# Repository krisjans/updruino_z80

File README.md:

# updruino_z80
Use Updruino FPGA boarad (iCE40-UP5K-SG48) as bridge between ZX Spectrum and Raspberry Pi

# warning!
This project uses iCE40-UP5K-SG48 in "CRAM" mode.

By default Updruino ships in "flash mode".

You must re-solder two 0Ohm resistors from Horizontal "Flash" positions to vertical "CRAM" positions.

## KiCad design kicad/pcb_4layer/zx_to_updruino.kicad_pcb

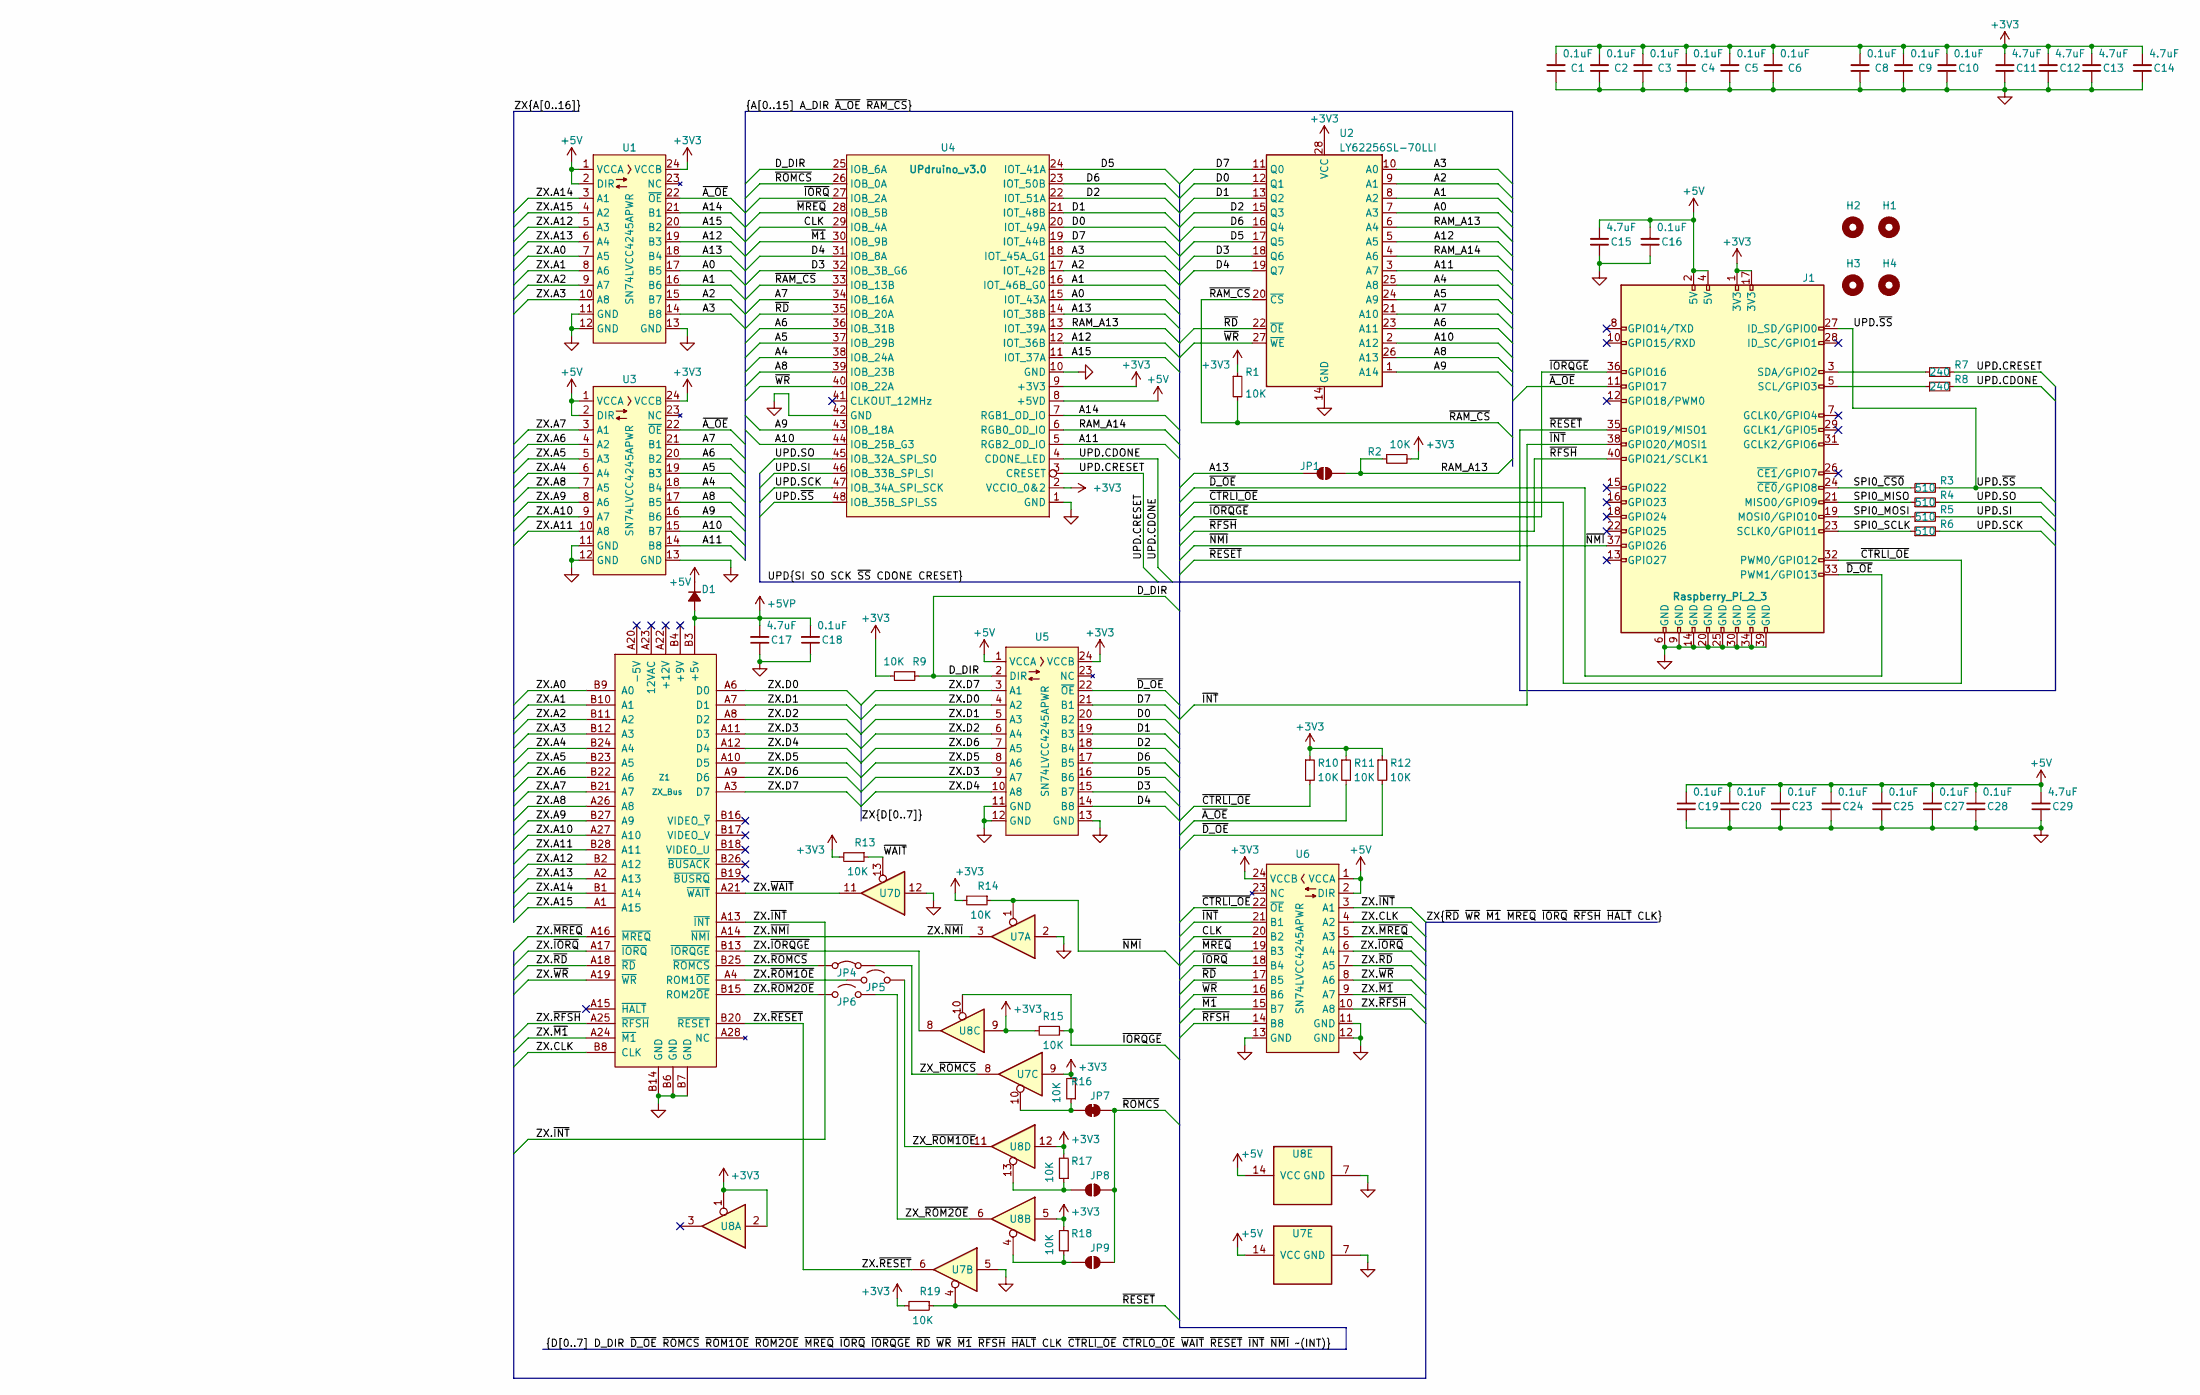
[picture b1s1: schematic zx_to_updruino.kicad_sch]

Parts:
C1, C2, C3, C4, C5, C6, C8, C9, C10, C16, C18, C19, C20, C23, C24, C25, C27, C28: 0.1uF; C_0805_2012Metric
C11, C12, C13, C14, C15, C17, C29: 4.7uF; C_0805_2012Metric
D1: B5819W SL; D_SOD-123; LCSC C8598
H1, H2, H3, H4: MountingHole
J1: Raspberry_Pi_2_3; PinSocket_2x20_P2.54mm_Vertical
JP1, JP8, JP9: SolderJumper_2_Bridged; SolderJumper-2_P1.3mm_Open_RoundedPad1.0x1.5mm
JP4, JP5, JP6: Jumper_2_Bridged; PinSocket_1x02_P2.54mm_Vertical
JP7: SolderJumper_2_Bridged; SolderJumper-2_P1.3mm_Bridged_RoundedPad1.0x1.5mm
R1, R2, R9, R10, R11, R12, R13, R14, R15, R16, R17, R18, R19: 10K; R_1206_3216Metric
R3, R4, R5, R6: 510; R_0805_2012Metric
R7, R8: 240; R_0805_2012Metric
U1, U3, U5, U6: SN74LVCC4245APWR; TSSOP-24_L7.8-W4.4-P0.65-LS6.4-BL; LCSC C7035
U2: LY62256SL-70LLI; SOP-28_L18.2-W8.5-P1.27-LS12.1-BL; LCSC C261868
U4: UPdruino_v3.0
U7, U8: 74HC125D; SOIC-14_L8.7-W3.9-P1.27-LS6.0-BL; LCSC C5598
Z1: ZX_Bus; ZX_Bus_Edge_Connector

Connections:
+3V3: C1.2, C2.2, C3.2, C4.2, C5.2, C6.2, C8.2, C9.2, C10.2, C11.2, C12.2, C13.2, C14.2, J1.1 (3V3), J1.17 (3V3), R1.1, R2.2, R9.2, R10.1, R11.1, R12.1, R13.2, R14.2, R15.2, R16.2, R17.2, R18.2, R19.2, U1.24 (VCCB), U2.28 (VCC), U3.24 (VCCB), U4.2 (VCCIO_0&2), U4.9 (+3V3), U5.24 (VCCB), U6.24 (VCCB), U7.9, U8.1, U8.2, U8.5, U8.9, U8.12
+5V: C15.2, C16.2, C19.2, C20.2, C23.2, C24.2, C25.2, C27.2, C28.2, C29.2, D1.1 (K), J1.2 (5V), J1.4 (5V), U1.1 (VCCA), U1.2 (DIR), U3.1 (VCCA), U3.2 (DIR), U4.8 (+5VD), U5.1 (VCCA), U6.1 (VCCA), U6.2 (DIR), U7.14 (VCC), U8.14 (VCC)
+5VP: C17.2, C18.2, D1.2 (A), Z1.B3 (+5v)
/A0: U1.17 (B5), U2.7 (A3), U4.15 (IOT_43A)
/A1: U1.16 (B6), U2.8 (A2), U4.16 (IOT_46B_G0)
/A2: U1.15 (B7), U2.9 (A1), U4.17 (IOT_42B)
/A3: U1.14 (B8), U2.10 (A0), U4.18 (IOT_45A_G1)
/A4: U2.25 (A8), U3.18 (B4), U4.38 (IOB_24A)
/A5: U2.24 (A9), U3.19 (B3), U4.37 (IOB_29B)
/A6: U2.23 (A11), U3.20 (B2), U4.36 (IOB_31B)
/A7: U2.21 (A10), U3.21 (B1), U4.34 (IOB_16A)
/A8: U2.26 (A13), U3.17 (B5), U4.39 (IOB_23B)
/A9: U2.1 (A14), U3.16 (B6), U4.43 (IOB_18A)
/A10: U2.2 (A12), U3.15 (B7), U4.44 (IOB_25B_G3)
/A11: U2.3 (A7), U3.14 (B8), U4.5 (RGB2_OD_IO)
/A12: U1.19 (B3), U2.5 (A5), U4.12 (IOT_36B)
/A13: JP1.1 (A), U1.18 (B4), U4.14 (IOT_38B)
/A14: U1.21 (B1), U4.7 (RGB1_OD_IO)
/A15: U1.20 (B2), U4.11 (IOT_37A)
/CLK: U4.29 (IOB_4A), U6.20 (B2)
/D0: U2.12 (Q1), U4.20 (IOT_49A), U5.20 (B2)
/D1: U2.13 (Q2), U4.21 (IOT_48B), U5.19 (B3)
/D2: U2.15 (Q3), U4.22 (IOT_51A), U5.18 (B4)
/D3: U2.18 (Q6), U4.32 (IOB_3B_G6), U5.15 (B7)
/D4: U2.19 (Q7), U4.31 (IOB_8A), U5.14 (B8)
/D5: U2.17 (Q5), U4.24 (IOT_41A), U5.16 (B6)
/D6: U2.16 (Q4), U4.23 (IOT_50B), U5.17 (B5)
/D7: U2.11 (Q0), U4.19 (IOT_44B), U5.21 (B1)
/D_DIR: R9.1, U4.25 (IOB_6A), U5.2 (DIR)
/RAM_A13: JP1.2 (B), R2.1, U2.6 (A4), U4.13 (IOT_39A)
/RAM_A14: U2.4 (A6), U4.6 (RGB0_OD_IO)
/SPI0_MISO: J1.21 (MISO0/GPIO9), R4.1
/SPI0_MOSI: J1.19 (MOSI0/GPIO10), R5.1
/SPI0_SCLK: J1.23 (SCLK0/GPIO11), R6.1
/SPI0_~CS0: J1.24 (~CE0/GPIO8), R3.1
/UPD.CDONE: R8.2, U4.4 (CDONE_LED)
/UPD.CRESET: R7.2, U4.3 (CRESET)
/UPD.SCK: R6.2, U4.47 (IOB_34A_SPI_SCK)
/UPD.SI: R5.2, U4.46 (IOB_33B_SPI_SI)
/UPD.SO: R4.2, U4.45 (IOB_32A_SPI_SO)
/UPD.~SS: J1.27 (ID_SD/GPIO0), R3.2, U4.48 (IOB_35B_SPI_SS)
/ZX.A0: U1.7 (A5), Z1.B9 (A0)
/ZX.A1: U1.8 (A6), Z1.B10 (A1)
/ZX.A2: U1.9 (A7), Z1.B11 (A2)
/ZX.A3: U1.10 (A8), Z1.B12 (A3)
/ZX.A4: U3.6 (A4), Z1.B24 (A4)
/ZX.A5: U3.5 (A3), Z1.B23 (A5)
/ZX.A6: U3.4 (A2), Z1.B22 (A6)
/ZX.A7: U3.3 (A1), Z1.B21 (A7)
/ZX.A8: U3.7 (A5), Z1.A26 (A8)
/ZX.A9: U3.8 (A6), Z1.B27 (A9)
/ZX.A10: U3.9 (A7), Z1.A27 (A10)
/ZX.A11: U3.10 (A8), Z1.B28 (A11)
/ZX.A12: U1.5 (A3), Z1.B2 (A12)
/ZX.A13: U1.6 (A4), Z1.A2 (A13)
/ZX.A14: U1.3 (A1), Z1.B1 (A14)
/ZX.A15: U1.4 (A2), Z1.A1 (A15)
/ZX.CLK: U6.4 (A2), Z1.B8 (CLK)
/ZX.D0: U5.4 (A2), Z1.A6 (D0)
/ZX.D1: U5.5 (A3), Z1.A7 (D1)
/ZX.D2: U5.6 (A4), Z1.A8 (D2)
/ZX.D3: U5.9 (A7), Z1.A11 (D3)
/ZX.D4: U5.10 (A8), Z1.A12 (D4)
/ZX.D5: U5.8 (A6), Z1.A10 (D5)
/ZX.D6: U5.7 (A5), Z1.A9 (D6)
/ZX.D7: U5.3 (A1), Z1.A3 (D7)
/ZX.~INT: U6.3 (A1), Z1.A13 (~INT)
/ZX.~IORQGE: U8.8, Z1.B13 (~IORQGE)
/ZX.~IORQ: U6.6 (A4), Z1.A17 (~IORQ)
/ZX.~M1: U6.9 (A7), Z1.A24 (~M1)
/ZX.~MREQ: U6.5 (A3), Z1.A16 (~MREQ)
/ZX.~NMI: U7.3, Z1.A14 (~NMI)
/ZX.~RD: U6.7 (A5), Z1.A18 (~RD)
/ZX.~RESET: U7.6, Z1.B20 (~RESET)
/ZX.~RFSH: U6.10 (A8), Z1.A25 (~RFSH)
/ZX.~ROM1OE: JP5.1 (A), Z1.A4 (ROM1~OE)
/ZX.~ROM2OE: JP6.1 (A), Z1.B15 (ROM2~OE)
/ZX.~ROMCS: JP4.1 (A), Z1.B25 (~ROMCS)
/ZX.~WAIT: U7.11, Z1.A21 (~WAIT)
/ZX.~WR: U6.8 (A6), Z1.A19 (~WR)
/ZX_~ROM1OE: JP5.2 (B), U8.11
/ZX_~ROM2OE: JP6.2 (B), U8.6
/ZX_~ROMCS: JP4.2 (B), U7.8
/~A_OE: J1.11 (GPIO17), R11.2, U1.22 (~OE), U3.22 (~OE)
/~CTRLI_OE: J1.32 (PWM0/GPIO12), R10.2, U6.22 (~OE)
/~INT: J1.38 (GPIO20/MOSI1), U6.21 (B1)
/~IORQGE: J1.36 (GPIO16), R15.1, U8.10
/~IORQ: U4.27 (IOB_2A), U6.18 (B4)
/~M1: U4.30 (IOB_9B), U6.15 (B7)
/~MREQ: U4.28 (IOB_5B), U6.19 (B3)
/~RAM_CS: R1.2, U2.20 (~CS), U4.33 (IOB_13B)
/~RD: U2.22 (~OE), U4.35 (IOB_20A), U6.17 (B5)
/~RESET: J1.35 (GPIO19/MISO1), R19.1, U7.4
/~RFSH: J1.40 (GPIO21/SCLK1), U6.14 (B8)
/~ROMCS: JP7.1 (A), JP8.2 (B), JP9.2 (B), U4.26 (IOB_0A)
/~WAIT: R13.1, U7.13
/~WR: U2.27 (~WE), U4.40 (IOB_22A), U6.16 (B6)
GND: C1.1, C2.1, C3.1, C4.1, C5.1, C6.1, C8.1, C9.1, C10.1, C11.1, C12.1, C13.1, C14.1, C15.1, C16.1, C17.1, C18.1, C19.1, C20.1, C23.1, C24.1, C25.1, C27.1, C28.1, C29.1, J1.6 (GND), J1.9 (GND), J1.14 (GND), J1.20 (GND), J1.25 (GND), J1.30 (GND), J1.34 (GND), J1.39 (GND), U1.11 (GND), U1.12 (GND), U1.13 (GND), U2.14 (GND), U3.11 (GND), U3.12 (GND), U3.13 (GND), U4.1 (GND), U4.10 (GND), U4.42 (GND), U5.11 (GND), U5.12 (GND), U5.13 (GND), U6.11 (GND), U6.12 (GND), U6.13 (GND), U7.2, U7.5, U7.7 (GND), U7.12, U8.7 (GND), Z1.B6 (GND), Z1.B7 (GND), Z1.B14 (GND)
unnamed: J1.3 (SDA/GPIO2), R7.1
unnamed: J1.5 (SCL/GPIO3), R8.1
unnamed: JP7.2 (B), R16.1, U7.10
unnamed: JP8.1 (A), R17.1, U8.13
unnamed: JP9.1 (A), R18.1, U8.4

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
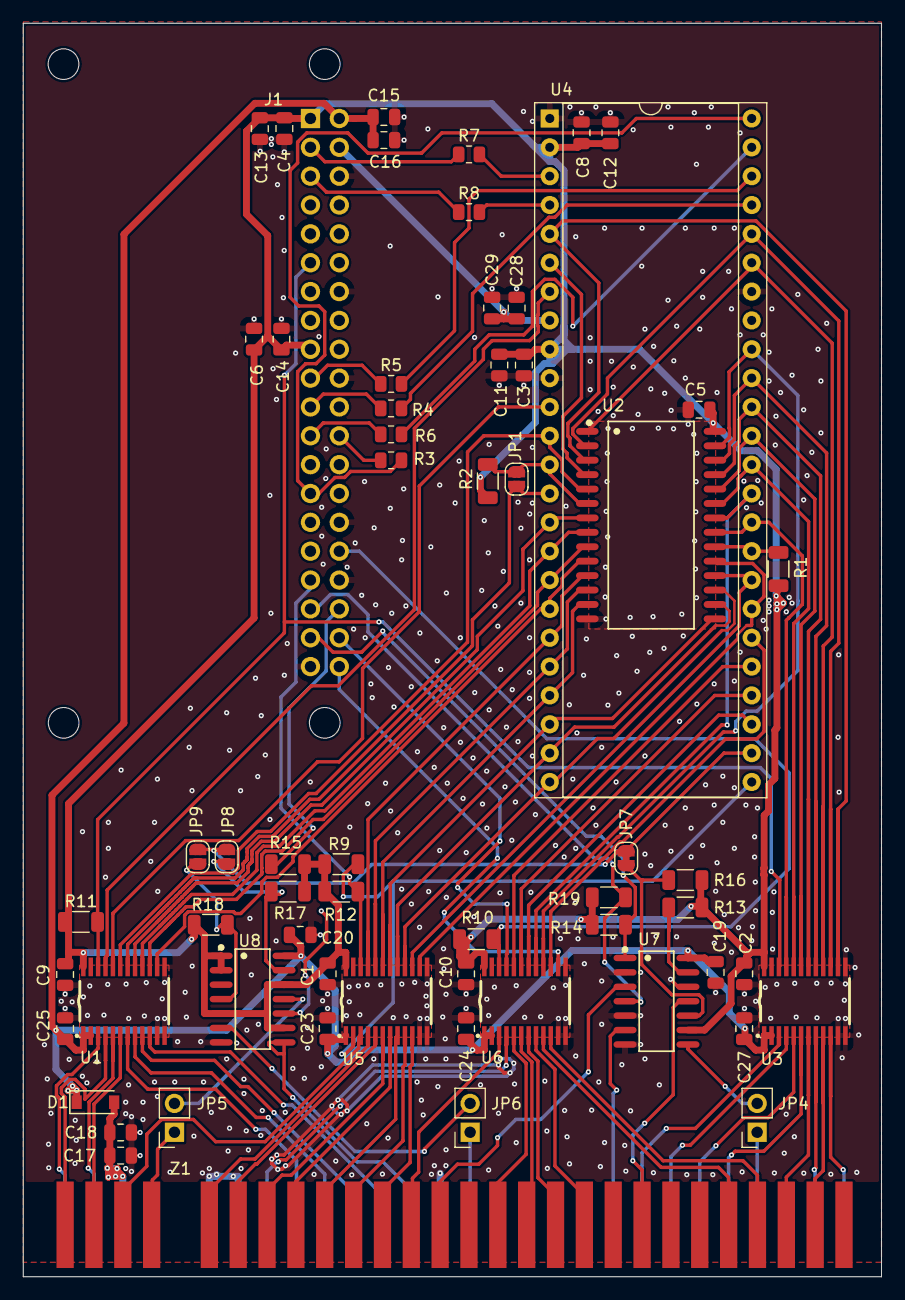
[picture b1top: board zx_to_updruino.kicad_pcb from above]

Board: 4 copper layers, 75.6 x 110.4 mm, 66 parts (1 on the bottom side), 105 nets.

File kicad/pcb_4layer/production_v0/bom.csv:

Designator,Footprint,Quantity,Value,LCSC Part #
"C1, C10, C16, C18, C19, C2, C20, C23, C24, C25, C27, C28, C3, C4, C5, C6, C8, C9",C_0805_2012Metric,18,0.1uF,
"C11, C12, C13, C14, C15, C17, C29",C_0805_2012Metric,7,4.7uF,
D1,D_SOD-123,1,B5819W SL,C8598
"R1, R10, R11, R12, R13, R14, R15, R16, R17, R18, R19, R2, R9",R_1206_3216Metric,13,10K,
"R3, R4, R5, R6",R_0805_2012Metric,4,510,
"R7, R8",R_0805_2012Metric,2,240,
"U1, U3, U5, U6",TSSOP-24_L7.8-W4.4-P0.65-LS6.4-BL,4,SN74LVCC4245APWR,C7035
U2,SOP-28_L18.2-W8.5-P1.27-LS12.1-BL,1,LY62256SL-70LLI,C261868
"U7, U8",SOIC-14_L8.7-W3.9-P1.27-LS6.0-BL,2,74HC125D,C5598

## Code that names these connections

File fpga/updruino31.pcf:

set_io z80_a[0]  32
set_io z80_a[1]  35
set_io z80_a[2]  31
set_io z80_a[3]  37
set_io z80_a[4]  13
set_io z80_a[5]  19
set_io z80_a[6]  18
set_io z80_a[7]   9
set_io z80_a[8]  21
set_io z80_a[9]  10
set_io z80_a[10] 20
set_io z80_a[11] 41
set_io z80_a[12] 25
set_io z80_a[13] 27
set_io z80_a[14] 40
set_io z80_a[15] 23
set_io z80_d[0]  43
set_io z80_d[1]  36
set_io z80_d[2]  42
set_io z80_d[3]  44
set_io z80_d[4]   4
set_io z80_d[5]  28
set_io z80_d[6]  38
set_io z80_d[7]  34
#set_io z80_d_oe  Raspberry Pi GPIO-13
set_io z80_d_dir  2
set_io z80_wr    12
set_io z80_rd    11
set_io z80_iorq  47
set_io z80_mreq  45
set_io z80_m1     3
set_io z80_romcs 46
set_io z80_clk   48

set_io ram_a13   26
set_io ram_a14   39
set_io ram_cs     6

set_io spi_ss    16
set_io spi_sck   15
set_io spi_si    17
set_io spi_so    14

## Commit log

2022-12-28 Switch on test_led if write to Z80 IO port 12345 happened; Switch off test_led if read from Z80 IO port 12345 happened;
2022-12-29 Add data bus; Write to IO port 12345 will store 8-bit value in FPGA; Read from IO port 12345 will read back stored 8-bit value;
2022-12-31 Add SPI-subordinate support; 8 bytes from Z80 IO ports to/from SPI;
2022-12-31 Add .vscode to .gitignore
2022-12-31 Move shared clock to top of file;
2022-12-31 Add PC test tool to test SPI using FTDI chip;
2022-12-31 Fix timing bug in FPGA: Z80 IO port read/write was clashing;
2022-12-31 Add Makefile for fpga;
2022-12-31 Add KiCad schematics;
2022-12-31 Add warning about CRAM mode
2023-01-06 Python test programm for Raspberry PI to send/receive using SPI;
2023-01-06 Python test programm for Raspberry PI to upload FPGA firmware in CRAM
2023-01-08 Enable Battery Charge Detection (USB charging cable) in FTDI chip on UPduino board;
    This is needed to allow normal SPI operation when not using UPduino FTDI USB;
2023-01-08 schematics: update breadboard: add Raspberry PI Zero and Spectrum ROMCS signal;
2023-01-08 testing: SPI over FTDI: set MSB first for SPI transactions;
2023-01-08 fpga: testing: set all test values to decimal;
2023-01-08 FPGA: FTDI: To program and use SPI need both - BCD and "self-powered";
2023-01-08 FPGA: implement 16k shadow-ROM using 15k block-RAM and 1K distributed-RAM;
    Active shadow-ROM using ZX Spectrum basic command 'OUT 12345,85' followed by reset;
2023-01-11 fpga: Add apio simulation target; move clk to top module
2023-01-11 Makefile: fpga: move building to "build" target; Print device utilisation summary at the end;
2023-01-12 fpga: use distributed rom as first 1024 bytes and block ram as the rest;
2023-01-13 Makefile: fix apio verify and build error detection;
2023-01-13 fpga: add meta-stability filters;
2023-01-13 fpga: simplify IO port and rom operation detection;
2023-01-30 Switch from breadboard to PCB;
2023-01-30 Switch to PCB: fix zx spectrum ROM disable signal polarity;
2023-02-03 Add z80 clock to top module;
2023-02-03 Make second 8k shadow memory block writable (0x2000-0x3fff);
2023-02-03 Move all SPI logic to separate module;
2023-02-03 Set Z80 IO ports as module parameters;
2023-02-04 FPGA: Use module parameters to specify IO address bit count for each IO port;
2023-02-04 Improve shadow-ROM support: add configurable shadow-ROM map-in/out IO port and four configurable instruction fetch addresses;
2023-02-04 FPGA: ftdi: test tool: print both hex and decimal values;
2023-02-04 FPGA: commented attribute to force synthesis of ROM using simple logic elements;
2023-03-28 kicad: PCB v0: Add 4 layer PCB schematics, pcb and production gerber files;
2023-03-28 kicad: add v0 schematic as pdf file;
